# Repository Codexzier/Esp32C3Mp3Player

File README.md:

# Esp32C3Mp3Player
 A simple MP3 Player with ESP32-C3.

Einfacher MP3 Player auf Basis eines **ESP32-C3 Dev Moduls** (Variante mit I²C auf
GPIO8 = SDA und GPIO9 = SCL, z.B. ESP32-C3 SuperMini). Die MP3s liegen nach Kategorien
sortiert in Ordnern auf einer SD Karte und werden über einen PCM5102 I2S DAC ausgegeben.

## Benötigte Bauteile

| Bauteil | Hinweis |
|---|---|
| ESP32-C3 Dev Modul | Variante SDA = GPIO8, SCL = GPIO9 |
| OLED Display 128x32 | SSD1306, I²C, Adresse 0x3C |
| SD Karten Leser | SPI, FAT32 formatierte SD Karte |
| PCM5102 I2S DAC Modul | "PCM5102 I2S IIS Lossless Digital Audio DAC Decoder" |
| 2 Taster | Schließer, gegen GND |
| Potentiometer 10 kΩ | linear, für die Lautstärke |
| 2 Widerstände 100 kΩ | Spannungsteiler für die Akku Messung |
| LiPo / Li-Ion Akku (1 Zelle) | mit Lade-/Schutzschaltung (z.B. TP4056) |

## Pin Belegung

| GPIO | Funktion | Anschluss am Modul |
|---|---|---|
| GPIO0 | ADC – Lautstärke | Potentiometer Schleifer (Mitte) |
| GPIO1 | ADC – Akku Messung | Mitte Spannungsteiler 100k/100k |
| GPIO2 | I2S Daten | PCM5102 **DIN** |
| GPIO3 | Taster 1 (Play / nächster Titel) | Taster gegen GND |
| GPIO4 | SPI SCK | SD Karte **SCK** |
| GPIO5 | SPI MISO | SD Karte **MISO** |
| GPIO6 | SPI MOSI | SD Karte **MOSI** |
| GPIO7 | SPI CS | SD Karte **CS** |
| GPIO8 | I²C SDA | OLED **SDA** |
| GPIO9 | I²C SCL | OLED **SCL** |
| GPIO10 | I2S Bit Clock | PCM5102 **BCK** |
| GPIO20 | Taster 2 (Stop / nächste Kategorie) | Taster gegen GND |
| GPIO21 | I2S Word Select | PCM5102 **LCK** |

### OLED Display 128x32

| OLED | ESP32-C3 |
|---|---|
| VCC | 3V3 |
| GND | GND |
| SDA | GPIO8 |
| SCL | GPIO9 |

### SD Karten Leser

| SD Modul | ESP32-C3 |
|---|---|
| VCC | 3V3 (bzw. 5V, wenn das Modul einen eigenen Spannungsregler hat) |
| GND | GND |
| SCK | GPIO4 |
| MISO | GPIO5 |
| MOSI | GPIO6 |
| CS | GPIO7 |

### PCM5102 I2S DAC

| PCM5102 | ESP32-C3 / Anschluss |
|---|---|
| VIN | 3V3 (oder 5V) |
| GND | GND |
| BCK | GPIO10 |
| DIN | GPIO2 |
| LCK | GPIO21 |
| SCK | **GND** (der DAC erzeugt den Systemtakt dann selbst) |
| FLT | GND (normaler Filter) |
| DEMP | GND (De-Emphasis aus) |
| XSMT | **3V3** (Soft-Mute aus, sonst bleibt der Ausgang stumm) |
| FMT | GND (I2S Format) |

Bei vielen PCM5102 Modulen sind FLT, DEMP, XSMT und FMT über Lötbrücken (H/L) auf der
Rückseite eingestellt und SCK ist schon mit GND verbunden – dann müssen diese Pins nicht
extra verdrahtet werden. Der Kopfhörer bzw. Verstärker kommt an den Line-Out (3,5 mm Klinke
oder L / G / R).

### Taster

Beide Taster schalten den GPIO gegen GND. Es werden die internen Pull-Up Widerstände
verwendet, externe Widerstände sind nicht nötig.

| Taster | ESP32-C3 | Funktion |
|---|---|---|
| Taster 1 | GPIO3 ↔ GND | Play, bei erneutem Drücken nächster Titel |
| Taster 2 | GPIO20 ↔ GND | Titel anhalten und zur nächsten Kategorie wechseln |

### Potentiometer (Lautstärke)

| Potentiometer | ESP32-C3 |
|---|---|
| Äußerer Pin 1 | GND |
| Schleifer (Mitte) | GPIO0 |
| Äußerer Pin 2 | 3V3 |

### Akku Messung

Der Akku wird über einen Spannungsteiler (2 × 100 kΩ) gemessen, damit am ADC maximal
ca. 2,1 V anliegen:

```
Akku + ──[100k]──┬──[100k]── GND
                 │
               GPIO1
```

Wird keine Akkuspannung erkannt (Betrieb nur über USB), zeigt die Akku Anzeige nur den
Rahmen und es findet keine Abschaltung statt.

### Hinweise zu den Pins

- GPIO20/21 sind beim ESP32-C3 die Pins der UART0 (RX/TX). Da sie hier für Taster 2 und
  den DAC verwendet werden, in der Arduino IDE **"USB CDC On Boot: Enabled"** einstellen,
  damit die serielle Konsole über den nativen USB Anschluss läuft.
- GPIO2, GPIO8 und GPIO9 sind Strapping Pins. Sie werden hier nur als Ausgang (DIN) bzw.
  für I²C genutzt, die Taster liegen bewusst nicht auf diesen Pins.

## Platine (PCB)

Im Ordner [`hardware/`](hardware/) liegt ein KiCad-Projekt (Schaltplan und geroutete Platine,
88 × 52 mm, 2 Lagen). Die Module werden auf beiden Seiten der Platine gesteckt: SuperMini,
OLED, Taster, Poti und Ein/Aus-Schalter auf der Oberseite, SD-Modul, PCM5102, HW-104
(PAM8403) und TP4056 auf der Unterseite. Die Pinbelegung ist dieselbe wie oben. Zusätzlich
sind der Akku-Pfad mit Lademodul, Schalter und Schottky-Diode sowie Kondensatoren gegen
Störgeräusche am Verstärker vorgesehen.

Einige Modulmaße sind geschätzt – vor der Bestellung bitte die Hinweise in der
[Platinen-README](hardware/README.md) beachten.

## SD Karte

Die SD Karte muss FAT32 formatiert sein. Jeder Ordner im Hauptverzeichnis ist eine
Kategorie, die MP3s liegen direkt in diesen Ordnern:

```
/Chillout/Titel 1.mp3
/Dokumentation/...
/Lofi/...
/Work/...
```

Werden auf der SD Karte keine Ordner gefunden, legt der Player die Ordner **Chillout**,
**Work**, **Dokumentation** und **Lofi** an und zeigt den Hinweis, dass noch keine MP3s
gespeichert sind. Standard Kategorie beim Einschalten ist *Chillout*.

## Bedienung / Anzeige

1. **Einschalten:** Schiebetüren Animation, danach der Start Text
   - Zeile 1: `ESP32 MP3 Player`
   - Zeile 2: `Press Play (Anzahl Titel)`
   - Zeile 3: `Kat: <Ordner>`
2. **Taster 1:** Wiedergabe startet
   - Zeile 1: Titel der MP3 (lange Titel laufen als Lauftext durch)
   - Zeile 2: `Anzahl Titel: <Anzahl>`
   - Erneutes Drücken spielt den nächsten Titel, nach dem letzten Titel geht es wieder
     beim ersten los. Ist ein Titel zu Ende, wird automatisch der nächste gespielt.
3. **Taster 2:** Wiedergabe wird angehalten und die nächste Kategorie (Ordner) gewählt.
   Es wird wieder der Start Text mit der neuen Kategorie angezeigt.
4. **Potentiometer:** Lautstärke, angezeigt als 2 Pixel hoher Balken in den unteren beiden
   Pixelzeilen (31 und 32).
5. **Akku:** Wird alle 30 Sekunden und bei jedem Titelwechsel gemessen und rechts als
   Balken angezeigt. Bei 1 % wird die Wiedergabe gestoppt und angezeigt:
   - Zeile 1: `Batteriestand: 1%`
   - Zeile 2: `Bitte Aufladen`
   - Zeile 3: `Abschaltung in 30s` (zählt herunter)

   Bei 0 Sekunden wird das Display abgeschaltet und der ESP32 geht in den Deep Sleep.
   Neustart über Reset bzw. Aus- und wieder Einschalten.

## Software

Arduino IDE mit dem **esp32** Board Paket von Espressif (Version 3.x), Board
**"ESP32C3 Dev Module"**, *USB CDC On Boot: Enabled*.

Benötigte Bibliotheken:

- Adafruit GFX Library
- Adafruit SSD1306
- [arduino-audio-tools](https://github.com/pschatzmann/arduino-audio-tools)
- [arduino-libhelix](https://github.com/pschatzmann/arduino-libhelix) (MP3 Decoder)

Die beiden Audio Bibliotheken sind nicht im Bibliotheksverwalter enthalten und werden als
ZIP von GitHub heruntergeladen und über *Sketch → Bibliothek einbinden → .ZIP-Bibliothek
hinzufügen* installiert.

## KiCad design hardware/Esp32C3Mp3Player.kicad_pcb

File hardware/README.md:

# Platine ESP32-C3 MP3 Player

KiCad-Projekt für eine doppelseitig bestückte Platine (88 × 52 mm, 2 Lagen). Alle Module
sitzen auf der Platine. Der ESP32-C3 SuperMini wird auf Buchsenleisten gesteckt.

> **Wichtig:** Die Maße und Pin-Positionen einiger Module sind geschätzt (siehe
> [Vor der Bestellung prüfen](#vor-der-bestellung-prüfen)). Bitte die Footprints mit den
> eigenen Modulen vergleichen und bei Bedarf in KiCad anpassen, bevor die Platine bestellt wird.

| Oberseite (Bedienseite) | Unterseite (von unten gesehen) |
|---|---|
|  |  |

Schaltplan: [Esp32C3Mp3Player-Schaltplan.pdf](Esp32C3Mp3Player-Schaltplan.pdf) bzw.
[bilder/schaltplan.png](bilder/schaltplan.png)

## Dateien

| Datei | Inhalt |
|---|---|
| `Esp32C3Mp3Player.kicad_pro` | KiCad-Projekt (Netzklassen: Signale 0,3 mm, Versorgung 0,6 mm) |
| `Esp32C3Mp3Player.kicad_sch` | Schaltplan |
| `Esp32C3Mp3Player.kicad_pcb` | Platine (geroutet, GND-Flächen auf beiden Lagen) |
| `Esp32C3Mp3Player.kicad_sym` | Symbole der Module |
| `Esp32C3Mp3Player.pretty/` | Footprints der Module |
| `fp-lib-table`, `sym-lib-table` | binden die beiden Projekt-Bibliotheken ein |

Erstellt mit KiCad 7.0. Die Dateien lassen sich mit KiCad 8 und 9 öffnen, beim Speichern werden
sie in das neue Format umgewandelt. Standardbauteile (Widerstände, Taster, ...) stammen aus den
KiCad-Standardbibliotheken.

## Aufbau

### Oberseite (Bedienseite)

| Ref | Bauteil | Lage |
|---|---|---|
| A1 | ESP32-C3 SuperMini auf 2 × Buchsenleiste 1×8 | links, USB-C an der linken Kante |
| DS1 | OLED 0,91" 128×32 | oben Mitte |
| SW1, SW2 | Taster 6×6 mm (Play/Next, Kategorie) | unter dem Display |
| RV1 | Poti 10k linear (9 mm, Alps RK09K o.ä.) | rechts |
| SW3 | Schiebeschalter Ein/Aus (C&K OS102011MA1Q, 2 mm Raster) | untere Kante, Hebel zeigt nach außen |
| R1, R2, C3, C4 | Spannungsteiler Akku, Filter-Kondensatoren | unter dem SuperMini |
| D1, C1, C2, C5 | Schottky-Diode, Elkos, 100 nF | freie Flächen |
| JP1, JP2 | Lötbrücken für die Versorgung von SD-Modul und DAC | Mitte unten |

### Unterseite

| Ref | Bauteil | Lage |
|---|---|---|
| A2 | MicroSD-Modul (SPI, 42 × 24 mm) | Mitte, Kartenschlitz an der oberen Kante |
| A3 | PCM5102 DAC | rechts unten, 3,5-mm-Klinke an der rechten Kante |
| A4 | HW-104 (PAM8403) | rechts oben, Poti-Achse an der oberen Kante |
| A5 | TP4056 USB-C Lademodul | links unten, USB-C an der linken Kante |
| J1 | Akku (JST-PH 2 mm) | links |
| J2, J3 | Lautsprecher links/rechts (JST-PH 2 mm) | rechts oben |
| R3, R4 | 10 k Vorwiderstände Audio | zwischen DAC und Verstärker |

Die Module auf der Unterseite werden ebenfalls auf **Buchsenleisten** gesteckt (8,5 mm hoch).
Dadurch ist genug Abstand zu den Lötstellen der Bauteile auf der Oberseite. Nur der **TP4056**
wird mit kurzen Stiftleisten-Pins direkt angelötet; unter ihm liegen deshalb keine Lötstellen.

## Schaltung

Die Pinbelegung des ESP32-C3 ist dieselbe wie in der [README](../README.md) und im Sketch:

| GPIO | Signal | GPIO | Signal |
|---|---|---|---|
| GPIO0 | Poti (Lautstärke) | GPIO6 | SD MOSI |
| GPIO1 | Akku-Messung | GPIO7 | SD CS |
| GPIO2 | I2S DIN → PCM5102 | GPIO8 | I²C SDA (OLED) |
| GPIO3 | Taster Play/Next | GPIO9 | I²C SCL (OLED) |
| GPIO4 | SD SCK | GPIO10 | I2S BCK → PCM5102 |
| GPIO5 | SD MISO | GPIO20 | Taster Kategorie |
| | | GPIO21 | I2S LCK → PCM5102 |

**Stromversorgung:** Akku (J1) → TP4056 (B+/B−) → OUT+ → Schalter SW3 → Schottky-Diode D1 →
5V-Pin des SuperMini. Geladen wird über die USB-C-Buchse des TP4056. Steckt USB am SuperMini,
läuft der Player über USB; D1 verhindert, dass dabei 5 V in den Akku zurückfließen. R1/R2 teilen
die Akkuspannung (hinter dem Schalter) für GPIO1. Ist der Schalter aus, misst die Firmware keinen
Akku und schaltet nicht ab.

**Audio:** PCM5102 L/R → R3/R4 (10 k) → Eingang HW-104 → Lautsprecher an J2/J3 (Brückenausgang:
L+/L− bzw. R+/R−, **nicht** mit GND verbinden). C1 (470 µF) und C2 (100 nF) sitzen direkt an der
Versorgung des Verstärkers, beide Lagen sind GND-Flächen. Das hilft gegen das Störgeräusch.
Ist es zu leise, R3/R4 durch Drahtbrücken ersetzen. SCK des PCM5102 liegt auf GND (interner Takt).

### Lötbrücken JP1 und JP2 (müssen geschlossen werden!)

Ohne Brücke bekommen SD-Modul bzw. DAC keinen Strom. Die mittlere Fläche (2) wird mit einer der
äußeren verbunden:

| Brücke | 1–2 (3,3 V) | 2–3 (5 V) |
|---|---|---|
| JP1 (SD-Modul) | SD-Modul ohne eigenen Spannungsregler | Catalex-Modul mit AMS1117-Regler |
| JP2 (PCM5102) | empfohlen | möglich (Modul hat eigene Regler) |

Hinweis zum Akkubetrieb: Am 5V-Pin liegen dann nur etwa 3,0 – 3,9 V (Akku minus Diode). Ein
SD-Modul mit AMS1117-Regler bekommt daran zu wenig Spannung. Für Akkubetrieb ein SD-Modul ohne
Regler an 3,3 V nehmen (JP1 auf 1–2).

## Stückliste

| Ref | Wert | Bauform / Footprint | Menge |
|---|---|---|---|
| A1 | ESP32-C3 SuperMini | + 2 × Buchsenleiste 1×8, 2,54 mm | 1 |
| DS1 | OLED 0,91" 128×32 I²C | + Buchsenleiste 1×4 | 1 |
| A2 | MicroSD-Modul SPI | + Buchsenleiste 1×6 | 1 |
| A3 | PCM5102 DAC | + Buchsenleisten 1×6 und 1×3 | 1 |
| A4 | HW-104 PAM8403 | + Buchsenleisten 1×5 und 1×4 | 1 |
| A5 | TP4056 USB-C mit Schutzschaltung | 4 einzelne Stiftleisten-Pins | 1 |
| SW1, SW2 | Taster | 6 × 6 mm THT | 2 |
| SW3 | Schiebeschalter 1×UM | C&K OS102011MA1Q (2 mm Raster, gewinkelt) | 1 |
| RV1 | 10 k linear | Alps RK09K stehend (9 mm) | 1 |
| R1, R2 | 100 k | 0207, Raster 7,62 mm | 2 |
| R3, R4 | 10 k | 0207, Raster 7,62 mm | 2 |
| C1 | 470 µF / 10 V | Elko radial 8 mm, Raster 3,5 mm | 1 |
| C5 | 100 µF / 10 V | Elko radial 5 mm, Raster 2 mm | 1 |
| C2, C3, C4 | 100 nF | Keramik, Raster 5 mm | 3 |
| D1 | 1N5817 | DO-41 | 1 |
| J1, J2, J3 | JST-PH 2-polig | B2B-PH-K, stehend | 3 |
| H1–H4 | Befestigungsloch M3 | | 4 |

## Bestückung

1. Lötbrücken JP1 und JP2 setzen (siehe oben).
2. Flache Bauteile auf der Oberseite: R1, R2, C3, C4 (unter dem SuperMini), D1, C2, C5.
3. Taster, Poti, Schiebeschalter, C1.
4. Buchsenleisten für SuperMini und OLED auf der Oberseite.
5. Unterseite: R3, R4, J1–J3, dann die Buchsenleisten für SD-Modul, PCM5102 und HW-104.
6. TP4056 mit kurzen Pins auf der Unterseite anlöten.
7. Module aufstecken.

Die Lötstellen der Buchsenleisten liegen jeweils auf der Gegenseite. Deshalb die Buchsenleisten
löten, bevor die Module aufgesteckt werden.

## Vor der Bestellung prüfen

Einige Datenblätter waren nicht erreichbar. Diese Angaben sind deshalb geschätzt:

| Modul | Annahme | Was prüfen |
|---|---|---|
| ESP32-C3 SuperMini | 22,52 × 18 mm, Reihenabstand 15,24 mm, Pin 1 (5V) 2 mm von der USB-Kante. Von oben, USB links: obere Reihe 5V, GND, 3V3, 4, 3, 2, 1, 0; untere Reihe 5, 6, 7, 8, 9, 10, 20, 21 | Reihenfolge der Pinreihen. Sind die Reihen vertauscht, lässt sich der SuperMini mit der Bauteilseite nach unten aufstecken (USB bleibt links). Besser: Footprint anpassen |
| OLED 0,91" | 38 × 12 mm, Pins GND, VCC, SCL, SDA | Bei manchen Modulen sind VCC und GND vertauscht! |
| MicroSD-Modul | 42 × 24 mm (Catalex-Bauform), Pins GND, VCC, MISO, MOSI, SCK, CS, 4 Löcher M2 | Pinreihenfolge und Lage der Befestigungslöcher |
| PCM5102 | 17 × 32 mm, Leiste SCK, BCK, DIN, LCK, GND, VIN an einer kurzen Seite, L/G/R an der langen Seite, Klinke an der anderen kurzen Seite | Größe und Lage aller Pins |
| HW-104 | 29,5 × 20,2 mm, Poti links; 5V, GND, L, G, R rechts; L+, L−, R−, R+ unten (Raster 2,54 mm) | am ungenauesten geschätzt – alle Pins prüfen |
| TP4056 | 28 × 17 mm, Pads OUT+, B+, B−, OUT− an der Schmalseite gegenüber USB-C | Abstand der Pads |
| Poti, Schalter, JST | Alps RK09K, C&K OS102011MA1Q, JST-PH | passen die eigenen Bauteile? Polarität des Akkusteckers (+ an Pin 1) |

**Footprint anpassen:** In KiCad den Footprint-Editor öffnen, Bibliothek `Esp32C3Mp3Player`,
Pads verschieben, speichern. Danach in der Platine *Werkzeuge → Footprints aus Bibliothek
aktualisieren* ausführen. Betroffene Leiterbahnen neu verlegen und die Flächen mit `B` neu
füllen. Anschließend den DRC laufen lassen.

**Bestellen:** *Datei → Fertigungsdateien → Gerber* (Lagen F/B.Cu, F/B.Mask, F/B.Silkscreen,
Edge.Cuts) und *Bohrdateien*. Die Mindestmaße (Leiterbahn 0,3 mm, Abstand 0,2 mm, Bohrung
0,4 mm) schafft jeder übliche Platinenhersteller.

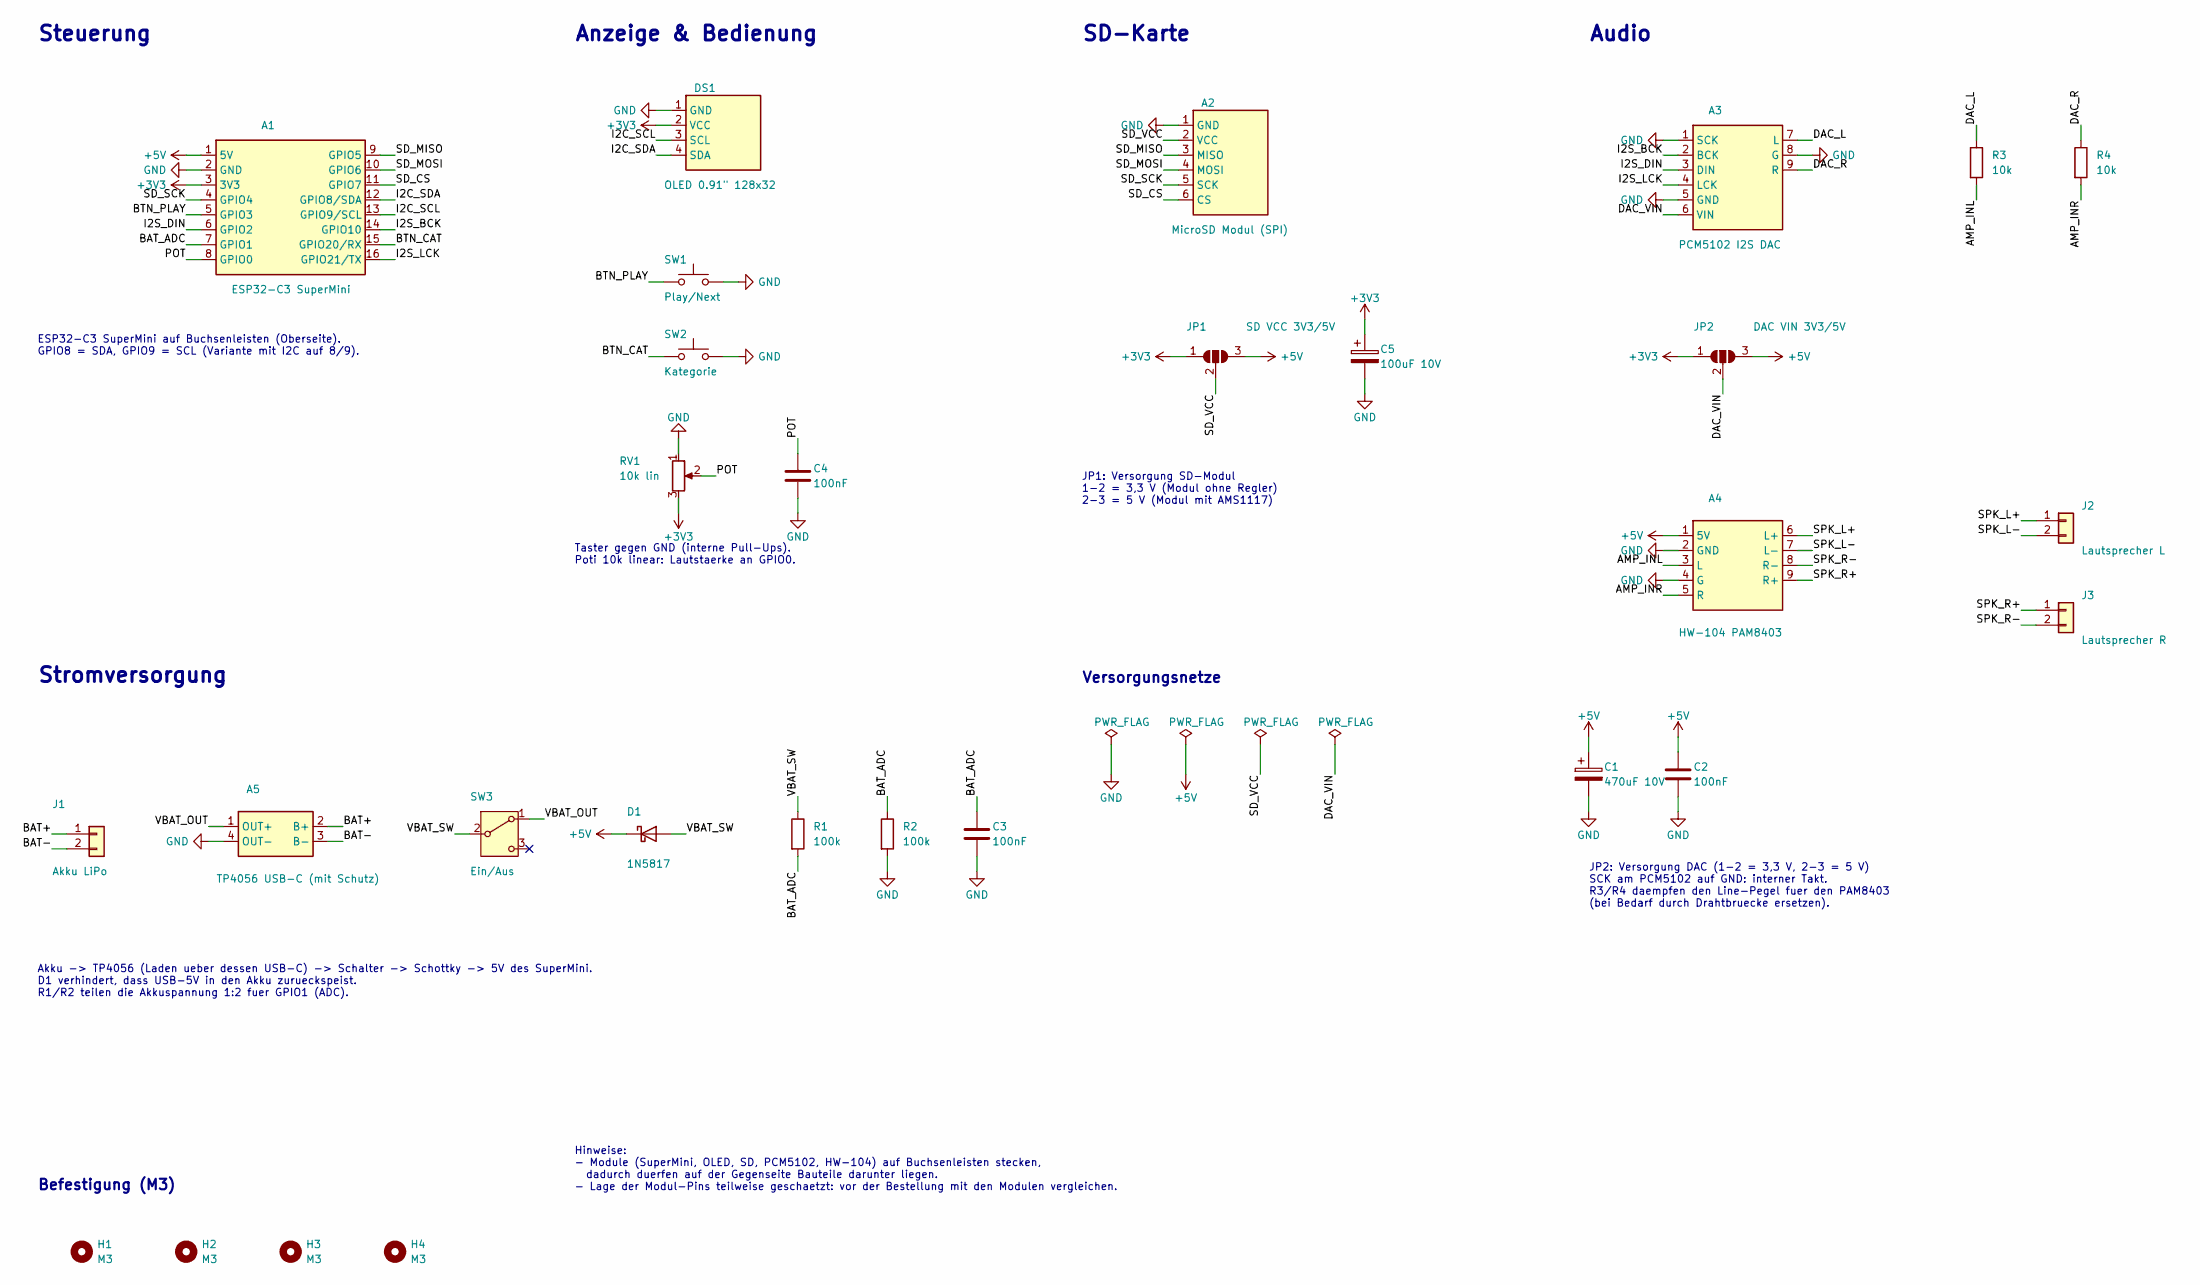
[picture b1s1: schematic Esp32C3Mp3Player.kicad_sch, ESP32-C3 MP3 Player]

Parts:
A1: ESP32-C3 SuperMini; ESP32-C3_SuperMini_Socket
A2: MicroSD Modul (SPI); SD_Card_Module_SPI_42x24mm
A3: PCM5102 I2S DAC; PCM5102_DAC_Module_17x32mm
A4: HW-104 PAM8403; HW-104_PAM8403_Module
A5: TP4056 USB-C (mit Schutz); TP4056_Module_USB-C_28x17mm
C1: 470uF 10V; CP_Radial_D8.0mm_P3.50mm
C2, C3, C4: 100nF; C_Disc_D5.0mm_W2.5mm_P5.00mm
C5: 100uF 10V; CP_Radial_D5.0mm_P2.00mm
D1: 1N5817; D_DO-41_SOD81_P10.16mm_Horizontal
DS1: OLED 0.91" 128x32; OLED_0.91in_128x32_I2C
H1, H2, H3, H4: M3; MountingHole_3.2mm_M3
J1: Akku LiPo; JST_PH_B2B-PH-K_1x02_P2.00mm_Vertical
J2: Lautsprecher L; JST_PH_B2B-PH-K_1x02_P2.00mm_Vertical
J3: Lautsprecher R; JST_PH_B2B-PH-K_1x02_P2.00mm_Vertical
JP1: SD VCC 3V3/5V; SolderJumper-3_P1.3mm_Open_RoundedPad1.0x1.5mm_NumberLabels
JP2: DAC VIN 3V3/5V; SolderJumper-3_P1.3mm_Open_RoundedPad1.0x1.5mm_NumberLabels
R1, R2: 100k; R_Axial_DIN0207_L6.3mm_D2.5mm_P7.62mm_Horizontal
R3, R4: 10k; R_Axial_DIN0207_L6.3mm_D2.5mm_P7.62mm_Horizontal
RV1: 10k lin; Potentiometer_Alps_RK09K_Single_Vertical
SW1: Play/Next; SW_PUSH_6mm
SW2: Kategorie; SW_PUSH_6mm
SW3: Ein/Aus; SW_Slide_SPDT_Angled_CK_OS102011MA1Q

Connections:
+3V3: A1.3 (3V3), C5.1, DS1.2 (VCC), JP1.1 (A), JP2.1 (A), RV1.3
+5V: A1.1 (5V), A4.1 (5V), C1.1, C2.1, D1.1 (K), JP1.3 (B), JP2.3 (B)
AMP_INL: A4.3 (L), R3.2
AMP_INR: A4.5 (R), R4.2
BAT+: A5.2 (B+), J1.1
BAT-: A5.3 (B-), J1.2
BAT_ADC: A1.7 (GPIO1), C3.1, R1.2, R2.1
BTN_CAT: A1.15 (GPIO20/RX), SW2.1
BTN_PLAY: A1.5 (GPIO3), SW1.1
DAC_L: A3.7 (L), R3.1
DAC_R: A3.9 (R), R4.1
DAC_VIN: A3.6 (VIN), JP2.2 (C)
GND: A1.2 (GND), A2.1 (GND), A3.1 (SCK), A3.5 (GND), A3.8 (G), A4.2 (GND), A4.4 (G), A5.4 (OUT-), C1.2, C2.2, C3.2, C4.2, C5.2, DS1.1 (GND), R2.2, RV1.1, SW1.2, SW2.2
I2C_SCL: A1.13 (GPIO9/SCL), DS1.3 (SCL)
I2C_SDA: A1.12 (GPIO8/SDA), DS1.4 (SDA)
I2S_BCK: A1.14 (GPIO10), A3.2 (BCK)
I2S_DIN: A1.6 (GPIO2), A3.3 (DIN)
I2S_LCK: A1.16 (GPIO21/TX), A3.4 (LCK)
POT: A1.8 (GPIO0), C4.1, RV1.2
SD_CS: A1.11 (GPIO7), A2.6 (CS)
SD_MISO: A1.9 (GPIO5), A2.3 (MISO)
SD_MOSI: A1.10 (GPIO6), A2.4 (MOSI)
SD_SCK: A1.4 (GPIO4), A2.5 (SCK)
SD_VCC: A2.2 (VCC), JP1.2 (C)
SPK_L+: A4.6 (L+), J2.1
SPK_L-: A4.7 (L-), J2.2
SPK_R+: A4.9 (R+), J3.1
SPK_R-: A4.8 (R-), J3.2
VBAT_OUT: A5.1 (OUT+), SW3.1 (A)
VBAT_SW: D1.2 (A), R1.1, SW3.2 (B)

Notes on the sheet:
Steuerung
ESP32-C3 SuperMini auf Buchsenleisten (Oberseite). GPIO8 = SDA, GPIO9 = SCL (Variante mit I2C auf 8/9).
Anzeige & Bedienung
Taster gegen GND (interne Pull-Ups). Poti 10k linear: Lautstaerke an GPIO0.
SD-Karte
JP1: Versorgung SD-Modul 1-2 = 3,3 V (Modul ohne Regler) 2-3 = 5 V (Modul mit AMS1117)
Audio
JP2: Versorgung DAC (1-2 = 3,3 V, 2-3 = 5 V) SCK am PCM5102 auf GND: interner Takt. R3/R4 daempfen den Line-Pegel fuer den PAM8403 (bei Bedarf durch Drahtbruecke ersetzen).
Stromversorgung
Akku -> TP4056 (Laden ueber dessen USB-C) -> Schalter -> Schottky -> 5V des SuperMini. D1 verhindert, dass USB-5V in den Akku zurueckspeist. R1/R2 teilen die Akkuspannung 1:2 fuer GPIO1 (ADC).
Versorgungsnetze
Befestigung (M3)
Hinweise: - Module (SuperMini, OLED, SD, PCM5102, HW-104) auf Buchsenleisten stecken, dadurch duerfen auf der Gegenseite Bauteile darunter liegen. - Lage der Modul-Pins teilweise geschaetzt: vor der Bestellung mit den Modulen vergleichen.

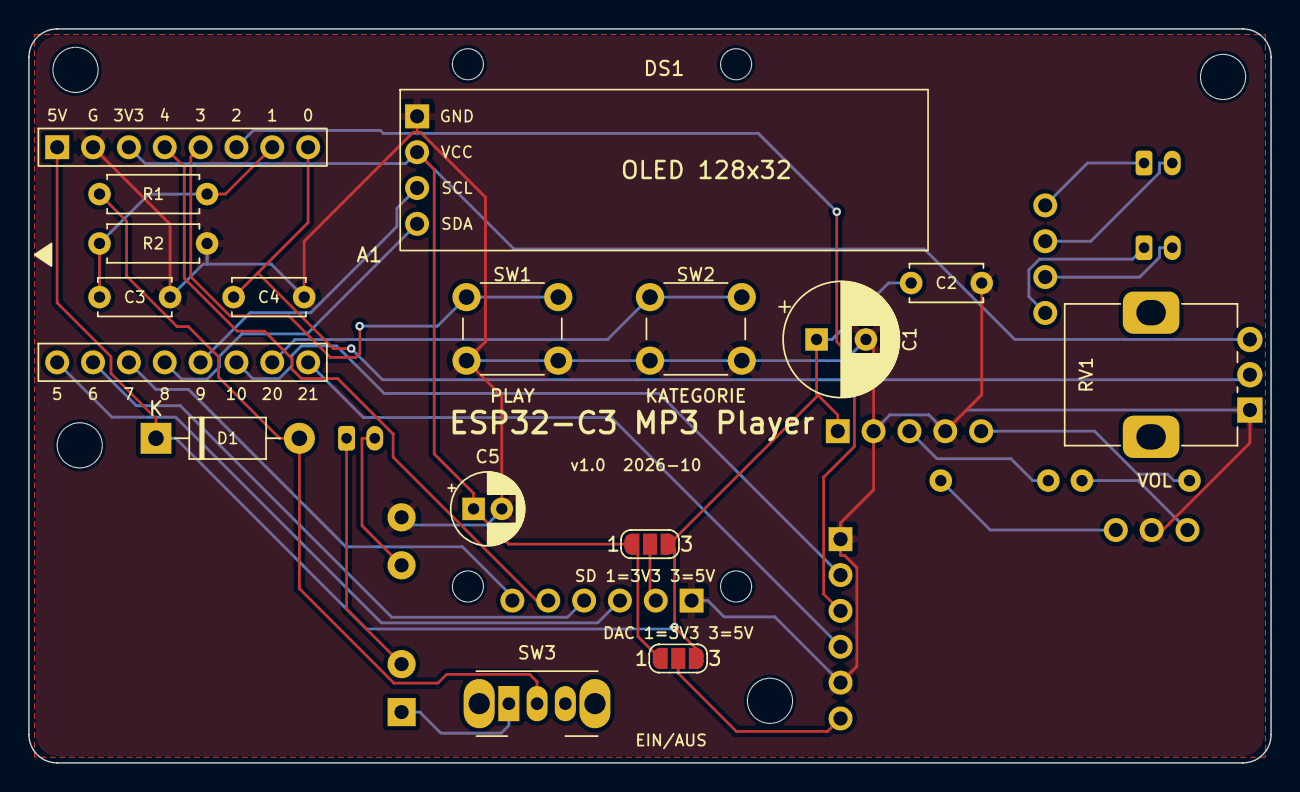
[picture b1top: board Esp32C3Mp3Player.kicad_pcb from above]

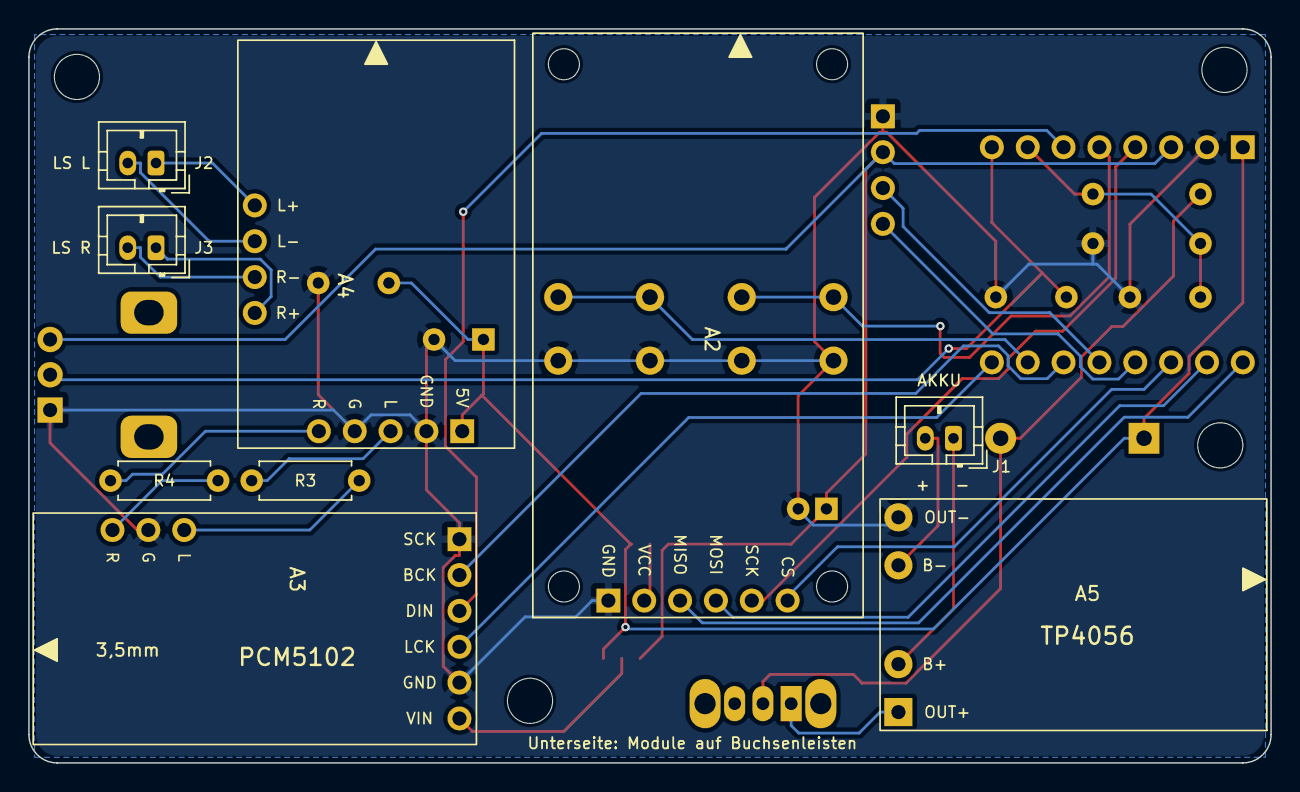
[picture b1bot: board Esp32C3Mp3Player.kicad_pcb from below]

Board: 2 copper layers, 88.0 x 52.0 mm, 29 parts (9 on the bottom side), 30 nets.

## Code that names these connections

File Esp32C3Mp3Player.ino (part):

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// ========================================================================================
// Projekt:       ESP32 MP3 Player
// Author:        Johannes P. Langner
// Controller:    ESP32-C3 DEV Module (Variante mit I2C: SDA = GPIO8, SCL = GPIO9)
// Description:   Einfacher MP3 Player
//                In den Ordner sind Kategorisch die MP3 nach Musik richtung angelegt.
//                - Chillout
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// Pin Belegung
// ========================================================================================
// I2C (OLED Display)
#define PIN_I2C_SDA        8
#define PIN_I2C_SCL        9

// SPI (SD Karten Leser)
#define PIN_SD_SCK         4
#define PIN_SD_MISO        5
#define PIN_SD_MOSI        6
#define PIN_SD_CS          7

// I2S (PCM5102 DAC)
#define PIN_DAC_BCK       10  // PCM5102: BCK
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  analogSetPinAttenuation(PIN_BATTERY, ADC_11db);

  // Display
  Wire.begin(PIN_I2C_SDA, PIN_I2C_SCL);
  Wire.setClock(400000);
  if (!display.begin(SSD1306_SWITCHCAPVCC, OLED_ADDRESS, true, false)) {
    for (;;); // Endlosschleife, wenn das Display nicht gefunden wird
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  display.display();

  // SD Karte
  SPI.begin(PIN_SD_SCK, PIN_SD_MISO, PIN_SD_MOSI, PIN_SD_CS);
  if (SD.begin(PIN_SD_CS, SPI, SD_SPI_FREQUENCY)) {
    initLibrary();
  }
  else {
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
